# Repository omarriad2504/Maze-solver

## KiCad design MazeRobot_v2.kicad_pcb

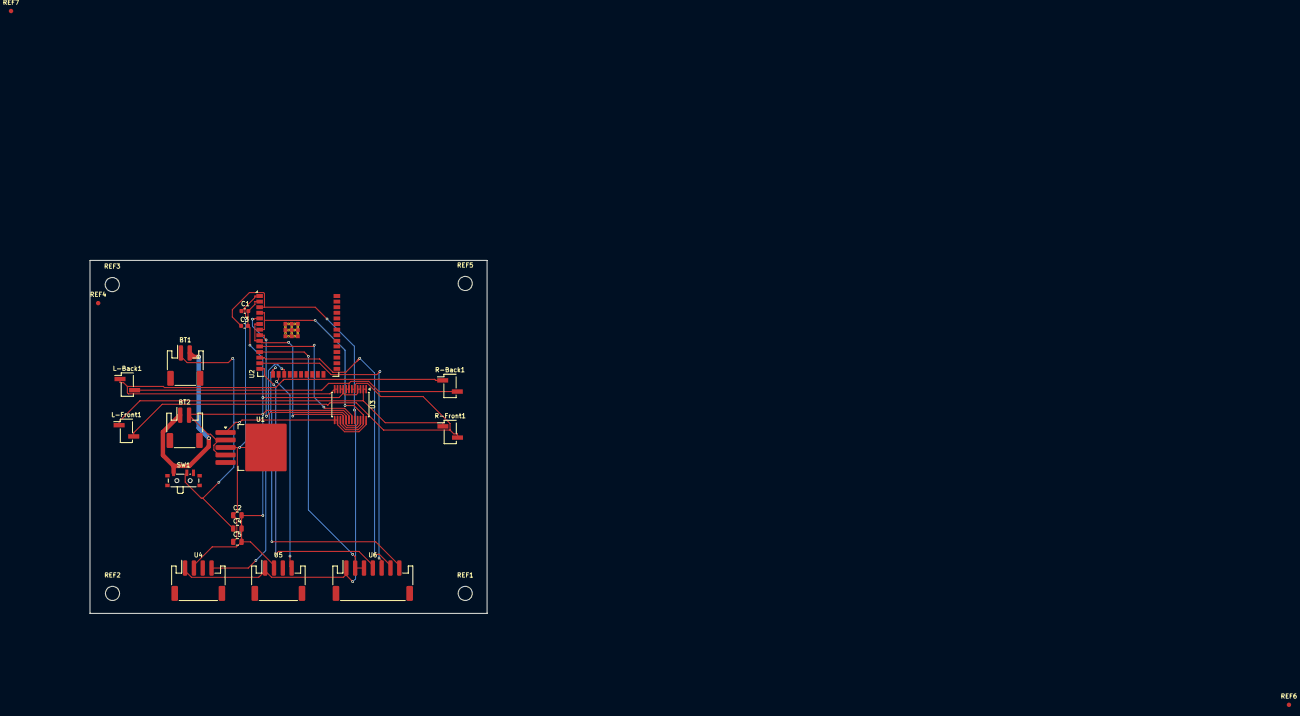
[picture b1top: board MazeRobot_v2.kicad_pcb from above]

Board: 2 copper layers, 90.0 x 80.0 mm, 25 parts (0 on the bottom side), 20 nets.

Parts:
BT1, BT2: Battery; JST_PH_S2B-PH-SM4-TB_1x02-1MP_P2.00mm_Horizontal
C1, C3: 0.1u; C_0603_1608Metric
C2, C4, C5: 10u; C_0805_2012Metric
L-Back1: Motor_DC; PinHeader_1x02_P2.54mm_Vertical_SMD_Pin1Left
L-Front1: Motor_DC; PinHeader_1x02_P2.54mm_Vertical_SMD_Pin1Left
R-Back1: Motor_DC; PinHeader_1x02_P2.54mm_Vertical_SMD_Pin1Left
R-Front1: Motor_DC; PinHeader_1x02_P2.54mm_Vertical_SMD_Pin1Left
REF1, REF2, REF3, REF5: MountingHole_3.2mm_M3
REF4, REF6, REF7: Fiducial_1mm_Mask2mm
SW1: SW_SPST; SW_SPDT_PCM12
U1: TO-263-5_TabPin3
U2: ESP32-WROOM-32E
U3: TB6612FNG; SSOP-24_5.3x8.2mm_P0.65mm
U4, U5: JST_PH_S4B-PH-SM4-TB_1x04-1MP_P2.00mm_Horizontal
U6: JST_PH_S7B-PH-SM4-TB_1x07-1MP_P2.00mm_Horizontal

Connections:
+3V3: C3.1, U2.3 (3V3), U3.20 (VCC), U4.1 (VCC(blue)), U5.1 (VCC(blue)), U6.1 (VCC)
+5V: C1.1, C2.1, C5.1, U1.3 (OUT+), U2.1 (VIN)
+7V4: BT1.1 (+), C4.1, SW1.2 (B), U1.1 (IN+), U3.13 (VM2), U3.14 (VM3), U3.24 (VM1)
/+7V4_RAW: BT1.2 (-), BT2.1 (+), SW1.1 (A)
/ENC_L: U2.16 (GPIO16), U5.4 (EncA(yellow))
/ENC_R: U2.17 (GPIO17), U4.4 (EncA(yellow))
GND: BT2.2 (-), C1.2, C2.2, C3.2, C4.2, C5.2, U1.2 (IN-), U1.4 (OUT-), U2.2 (GND), U3.3 (PGND1), U3.4 (PGND1), U3.9 (PGND2), U3.10 (PGND2), U3.18 (GND), U4.2 (GND(green)), U5.2 (GND(green))
unnamed: L-Back1.1 (+), R-Back1.1 (+), U3.11 (BO1), U3.12 (BO1)
unnamed: L-Back1.2 (-), R-Back1.2 (-), U3.7 (BO2), U3.8 (BO2)
unnamed: L-Front1.1 (+), R-Front1.1 (+), U3.1 (AO1), U3.2 (AO1)
unnamed: L-Front1.2 (-), R-Front1.2 (-), U3.5 (AO2), U3.6 (AO2)
unnamed: U2.10 (GPIO13), U3.19 (STBY)
unnamed: U2.6 (GPIO25), U2.9 (GPIO14), U3.16 (BIN2), U3.22 (AIN2)
unnamed: U2.15 (GPIO18), U6.7 (S5)
unnamed: U2.14 (GPIO19), U6.4 (S2)
unnamed: U2.13 (GPIO21), U6.5 (S3)
unnamed: U2.12 (GPIO22), U6.6 (S4)
unnamed: U2.11 (GPIO23), U6.2 (GND), U6.3 (S1)
unnamed: U2.4 (GPIO32), U2.7 (GPIO26), U3.15 (PWMB), U3.23 (PWMA)
unnamed: U2.5 (GPIO33), U2.8 (GPIO27), U3.17 (BIN1), U3.21 (AIN1)

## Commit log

2026-04-16 Create code
2026-04-17 softeware architecture
2026-04-17 Create code2
